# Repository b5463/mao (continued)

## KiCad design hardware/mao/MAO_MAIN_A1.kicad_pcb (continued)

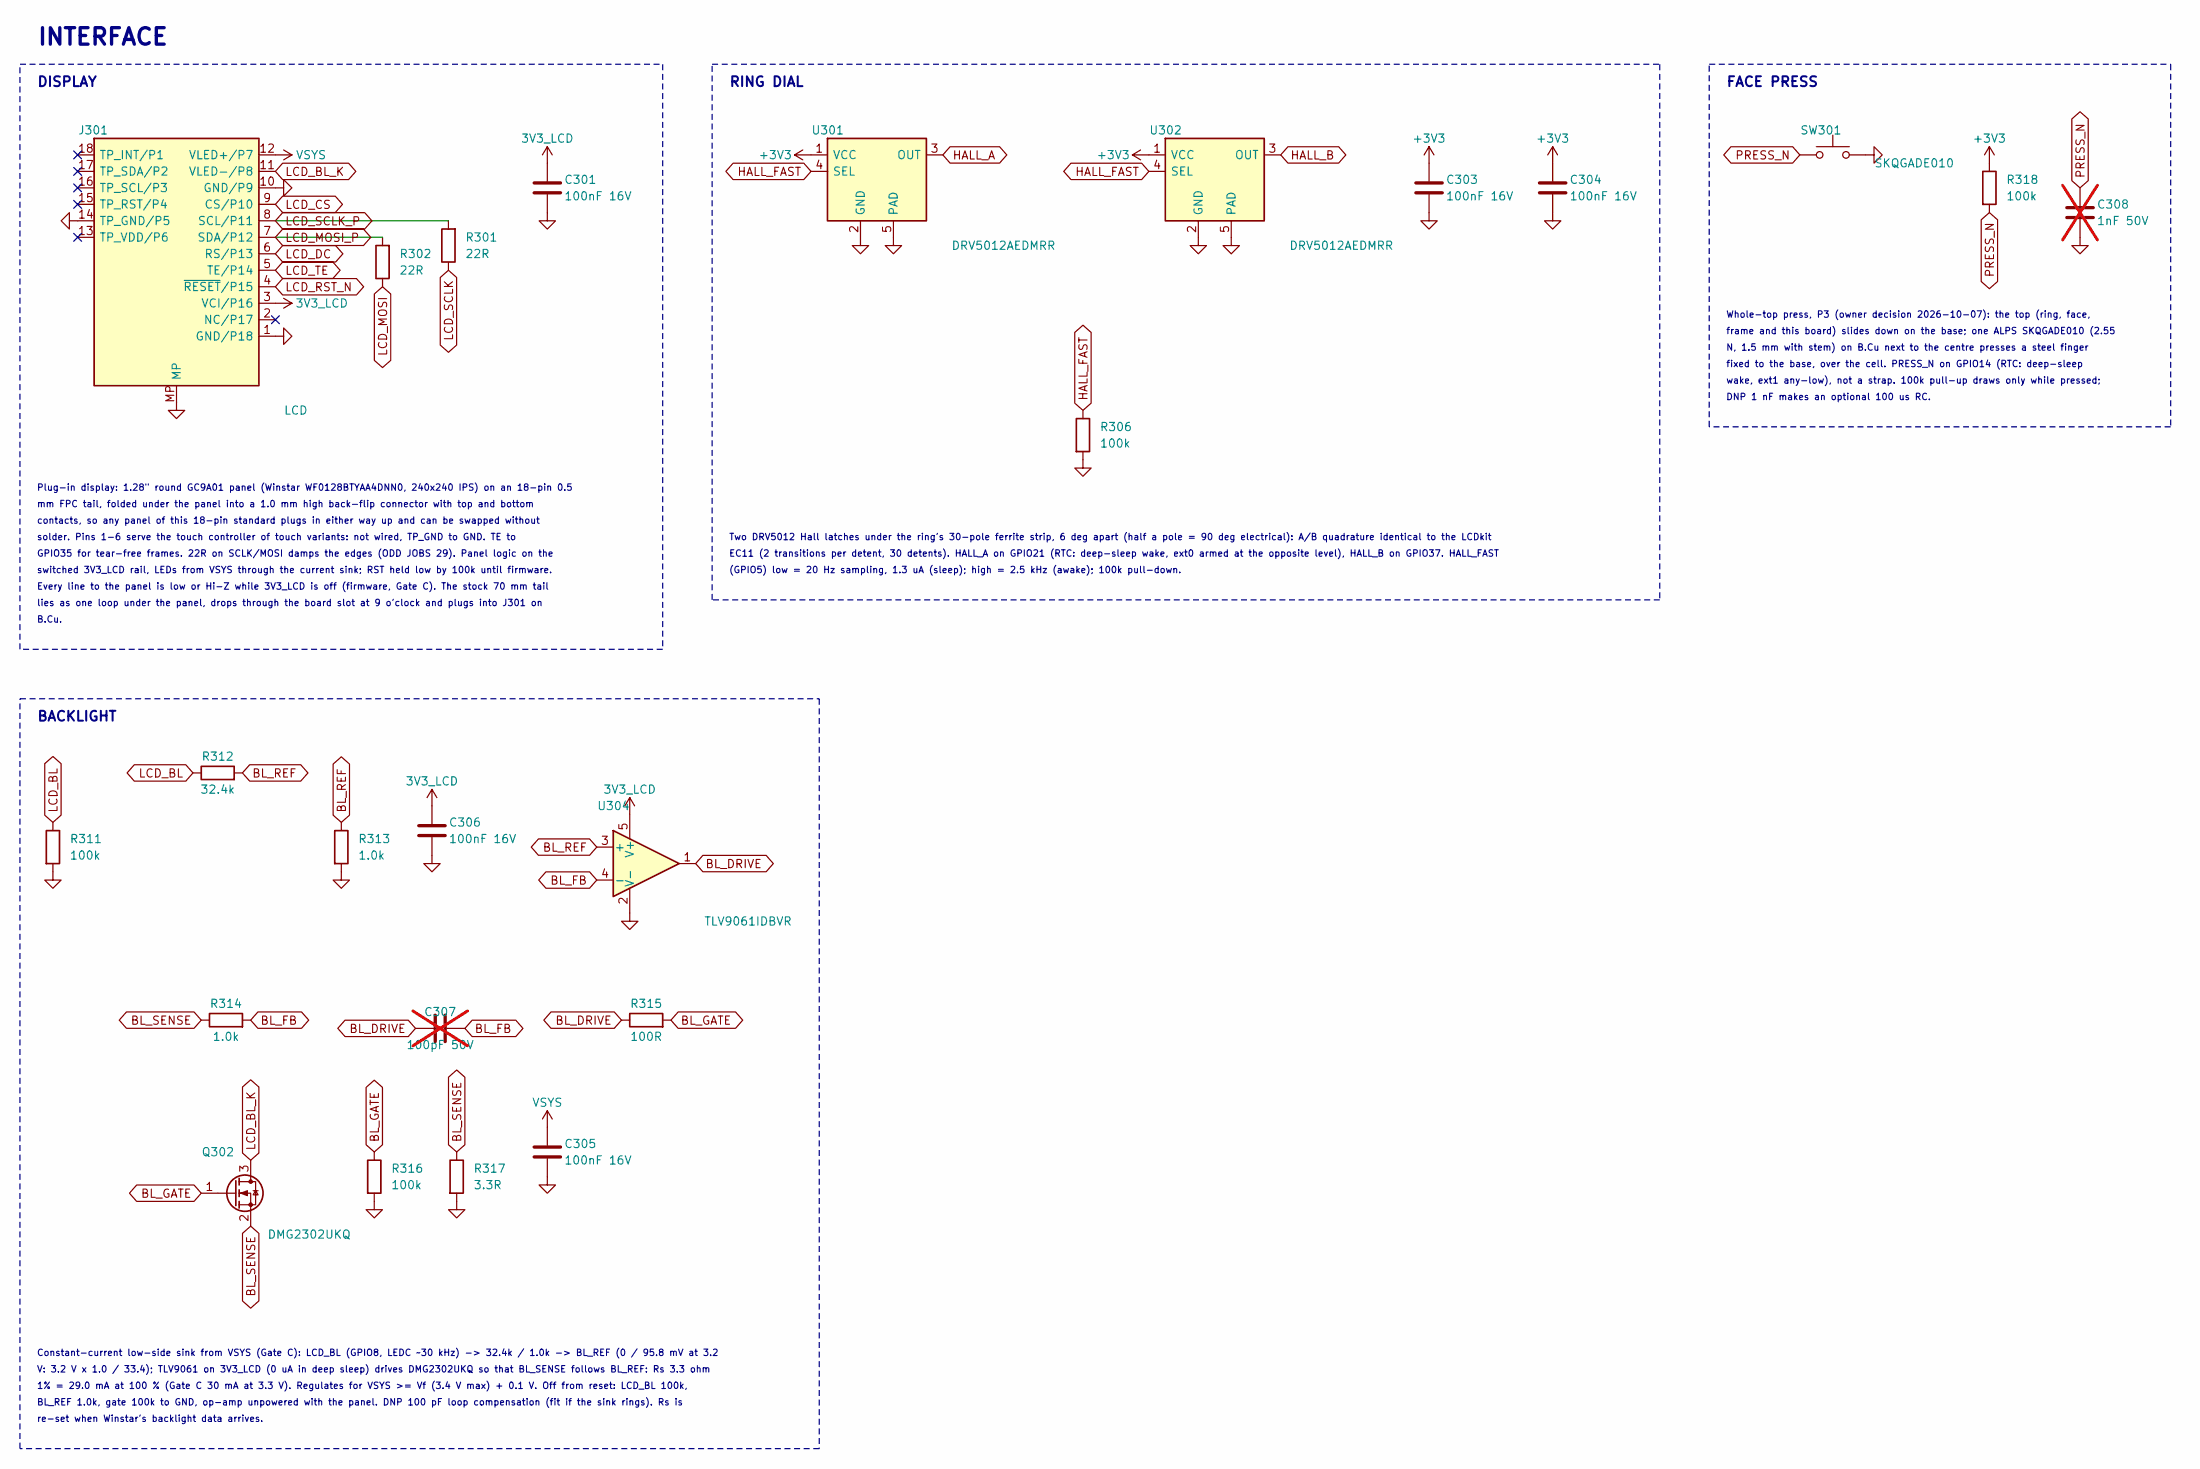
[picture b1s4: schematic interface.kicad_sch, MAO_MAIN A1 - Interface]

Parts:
C301, C303, C304, C305, C306: 100nF 16V; C_0402_1005Metric; MPN CL05B104KO5NNNC; LCSC C1525
C307: 100pF 50V; C_0402_1005Metric; MPN CL05C101JB5NNNC; LCSC C26409; not fitted
C308: 1nF 50V; C_0402_1005Metric; MPN CL05B102KB5NNNC; LCSC C14442; not fitted
J301: LCD; HDGC_0.5K-HX-18PWB_1x18-1MP_P0.5mm_Horizontal; MPN 0.5K-HX-18PWB; LCSC C2919497
Q302: DMG2302UKQ; SOT-23; MPN DMG2302UKQ-7; LCSC C5224573
R301, R302: 22R; R_0402_1005Metric; MPN 0402WGF220JTCE; LCSC C25092
R306, R311, R316, R318: 100k; R_0402_1005Metric; MPN 0402WGF1003TCE; LCSC C25741
R312: 32.4k; R_0402_1005Metric; MPN 0402WGF3242TCE; LCSC C26974
R313, R314: 1.0k; R_0402_1005Metric; MPN 0402WGF1001TCE; LCSC C11702
R315: 100R; R_0402_1005Metric; MPN 0402WGF1000TCE; LCSC C25076
R317: 3.3R; R_0603_1608Metric; MPN 0603WAF330KT5E; LCSC C22979
SW301: SKQGADE010; SW_SPST_SKQG_WithStem; MPN SKQGADE010; LCSC C116647
U301, U302: DRV5012AEDMRR; Texas_X2SON-4-1EP_1.1x1.4mm_P0.5mm_EP0.8x0.6mm; MPN DRV5012AEDMRR; LCSC C2655038
U304: TLV9061IDBVR; SOT-23-5; MPN TLV9061IDBVR; LCSC C398358

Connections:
3V3_LCD: C301.1, C306.1, J301.3 (VCI/P16), U304.5 (V+); also elsewhere on the board
+3V3: C303.1, C304.1, R318.1, U301.1 (VCC), U302.1 (VCC); also elsewhere on the board
BL_DRIVE: C307.1, R315.1, U304.1
BL_FB: C307.2, R314.2, U304.4 (-)
BL_GATE: Q302.1 (G), R315.2, R316.1
BL_REF: R312.2, R313.1, U304.3 (+)
BL_SENSE: Q302.2 (S), R314.1, R317.1
GND: C301.2, C303.2, C304.2, C305.2, C306.2, C308.2, J301.1 (GND/P18), J301.10 (GND/P9), J301.14 (TP_GND/P5), J301.MP, R306.2, R311.2, R313.2, R316.2, R317.2, SW301.2, U301.2 (GND), U301.5 (PAD), U302.2 (GND), U302.5 (PAD), U304.2 (V-); also elsewhere on the board
HALL_A: U301.3 (OUT); also elsewhere on the board
HALL_B: U302.3 (OUT); also elsewhere on the board
HALL_FAST: R306.1, U301.4 (SEL), U302.4 (SEL); also elsewhere on the board
LCD_BL: R311.1, R312.1; also elsewhere on the board
LCD_BL_K: J301.11 (VLED-/P8), Q302.3 (D)
LCD_CS: J301.9 (CS/P10); also elsewhere on the board
LCD_DC: J301.6 (RS/P13); also elsewhere on the board
LCD_MOSI: R302.1; also elsewhere on the board
LCD_MOSI_P: J301.7 (SDA/P12), R302.2
LCD_RST_N: J301.4 (~RESET/P15); also elsewhere on the board
LCD_SCLK: R301.1; also elsewhere on the board
LCD_SCLK_P: J301.8 (SCL/P11), R301.2
LCD_TE: J301.5 (TE/P14); also elsewhere on the board
PRESS_N: C308.1, R318.2, SW301.1; also elsewhere on the board
VSYS: C305.1, J301.12 (VLED+/P7); also elsewhere on the board

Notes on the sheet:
INTERFACE
DISPLAY
Plug-in display: 1.28" round GC9A01 panel (Winstar WF0128BTYAA4DNN0, 240x240 IPS) on an 18-pin 0.5
mm FPC tail, folded under the panel into a 1.0 mm high back-flip connector with top and bottom
contacts, so any panel of this 18-pin standard plugs in either way up and can be swapped without
solder. Pins 1-6 serve the touch controller of touch variants: not wired, TP_GND to GND. TE to
GPIO35 for tear-free frames. 22R on SCLK/MOSI damps the edges (ODD JOBS 29). Panel logic on the
switched 3V3_LCD rail, LEDs from VSYS through the current sink; RST held low by 100k until firmware.
Every line to the panel is low or Hi-Z while 3V3_LCD is off (firmware, Gate C). The stock 70 mm tail
lies as one loop under the panel, drops through the board slot at 9 o'clock and plugs into J301 on
B.Cu.
RING DIAL
Two DRV5012 Hall latches under the ring's 30-pole ferrite strip, 6 deg apart (half a pole = 90 deg electrical): A/B quadrature identical to the LCDkit
EC11 (2 transitions per detent, 30 detents). HALL_A on GPIO21 (RTC: deep-sleep wake, ext0 armed at the opposite level), HALL_B on GPIO37. HALL_FAST
(GPIO5) low = 20 Hz sampling, 1.3 uA (sleep); high = 2.5 kHz (awake); 100k pull-down.
FACE PRESS
Whole-top press, P3 (owner decision 2026-10-07): the top (ring, face,
frame and this board) slides down on the base; one ALPS SKQGADE010 (2.55
N, 1.5 mm with stem) on B.Cu next to the centre presses a steel finger
fixed to the base, over the cell. PRESS_N on GPIO14 (RTC: deep-sleep
wake, ext1 any-low), not a strap. 100k pull-up draws only while pressed;
DNP 1 nF makes an optional 100 us RC.
BACKLIGHT
Constant-current low-side sink from VSYS (Gate C): LCD_BL (GPIO8, LEDC ~30 kHz) -> 32.4k / 1.0k -> BL_REF (0 / 95.8 mV at 3.2
V: 3.2 V x 1.0 / 33.4); TLV9061 on 3V3_LCD (0 uA in deep sleep) drives DMG2302UKQ so that BL_SENSE follows BL_REF: Rs 3.3 ohm
1% = 29.0 mA at 100 % (Gate C 30 mA at 3.3 V). Regulates for VSYS >= Vf (3.4 V max) + 0.1 V. Off from reset: LCD_BL 100k,
BL_REF 1.0k, gate 100k to GND, op-amp unpowered with the panel. DNP 100 pF loop compensation (fit if the sink rings). Rs is
re-set when Winstar's backlight data arrives.

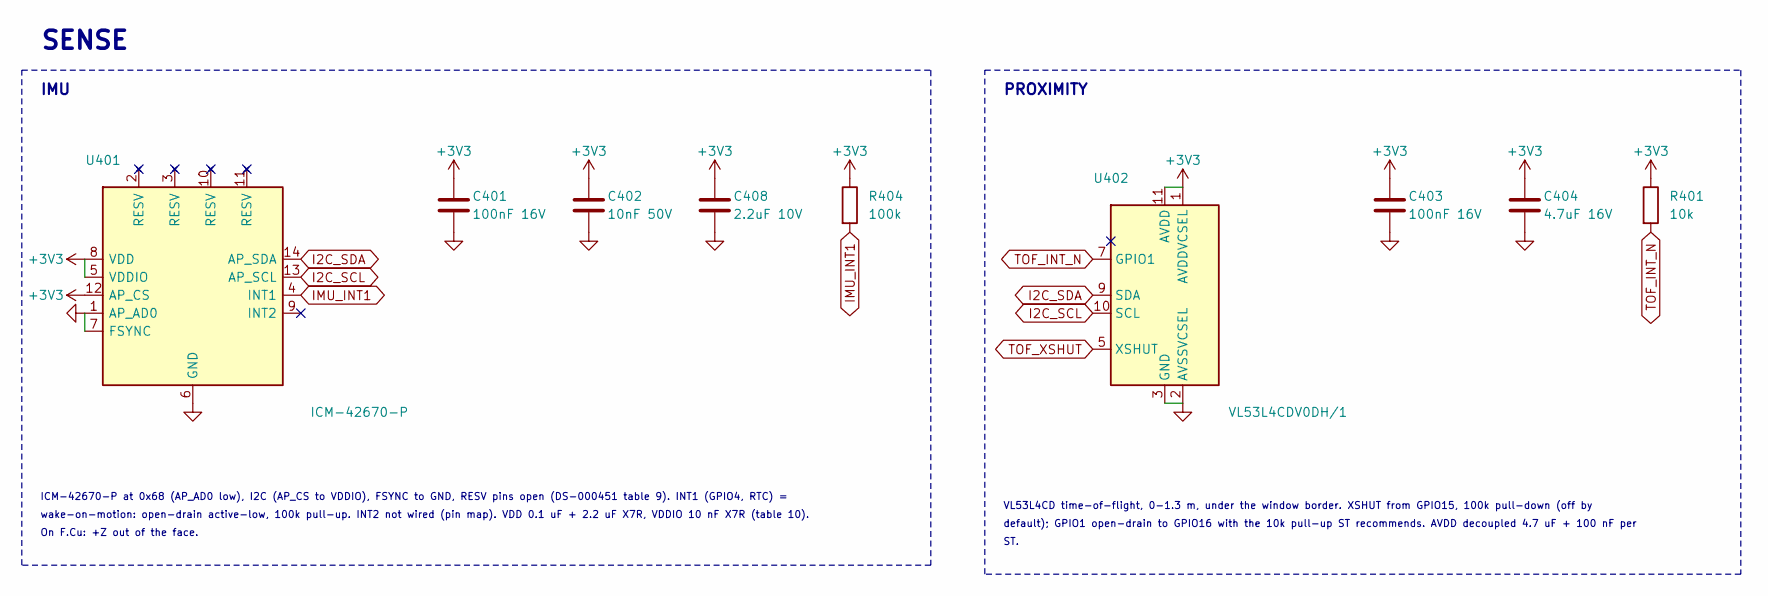
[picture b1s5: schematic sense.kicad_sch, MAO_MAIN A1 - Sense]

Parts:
C401, C403: 100nF 16V; C_0402_1005Metric; MPN CL05B104KO5NNNC; LCSC C1525
C402: 10nF 50V; C_0402_1005Metric; MPN CL05B103KB5NNNC; LCSC C15195
C404: 4.7uF 16V; C_0603_1608Metric; MPN CL10A475KO8NNNC; LCSC C19666
C408: 2.2uF 10V; C_0603_1608Metric; MPN CL10B225KP8NNNC; LCSC C100082
R401: 10k; R_0402_1005Metric; MPN 0402WGF1002TCE; LCSC C25744
R404: 100k; R_0402_1005Metric; MPN 0402WGF1003TCE; LCSC C25741
U401: ICM-42670-P; LGA-14_3x2.5mm_P0.5mm_LayoutBorder3x4y; MPN ICM-42670-P; LCSC C3288646
U402: VL53L4CDV0DH/1; ST_VL53L0X; MPN VL53L4CDV0DH/1; LCSC C3178291

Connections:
+3V3: C401.1, C402.1, C403.1, C404.1, C408.1, R401.1, R404.1, U401.5 (VDDIO), U401.8 (VDD), U401.12 (AP_CS), U402.1 (AVDDVCSEL), U402.11 (AVDD); also elsewhere on the board
GND: C401.2, C402.2, C403.2, C404.2, C408.2, U401.1 (AP_AD0), U401.6 (GND), U401.7 (FSYNC), U402.2 (AVSSVCSEL), U402.3 (GND), U402.4 (GND), U402.6 (GND), U402.12 (GND); also elsewhere on the board
I2C_SCL: U401.13 (AP_SCL), U402.10 (SCL); also elsewhere on the board
I2C_SDA: U401.14 (AP_SDA), U402.9 (SDA); also elsewhere on the board
IMU_INT1: R404.2, U401.4 (INT1); also elsewhere on the board
TOF_INT_N: R401.2, U402.7 (GPIO1); also elsewhere on the board
TOF_XSHUT: U402.5 (XSHUT); also elsewhere on the board

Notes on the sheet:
SENSE
IMU
ICM-42670-P at 0x68 (AP_AD0 low), I2C (AP_CS to VDDIO), FSYNC to GND, RESV pins open (DS-000451 table 9). INT1 (GPIO4, RTC) =
wake-on-motion: open-drain active-low, 100k pull-up. INT2 not wired (pin map). VDD 0.1 uF + 2.2 uF X7R, VDDIO 10 nF X7R (table 10).
On F.Cu: +Z out of the face.
PROXIMITY
VL53L4CD time-of-flight, 0-1.3 m, under the window border. XSHUT from GPIO15, 100k pull-down (off by
default); GPIO1 open-drain to GPIO16 with the 10k pull-up ST recommends. AVDD decoupled 4.7 uF + 100 nF per
ST.

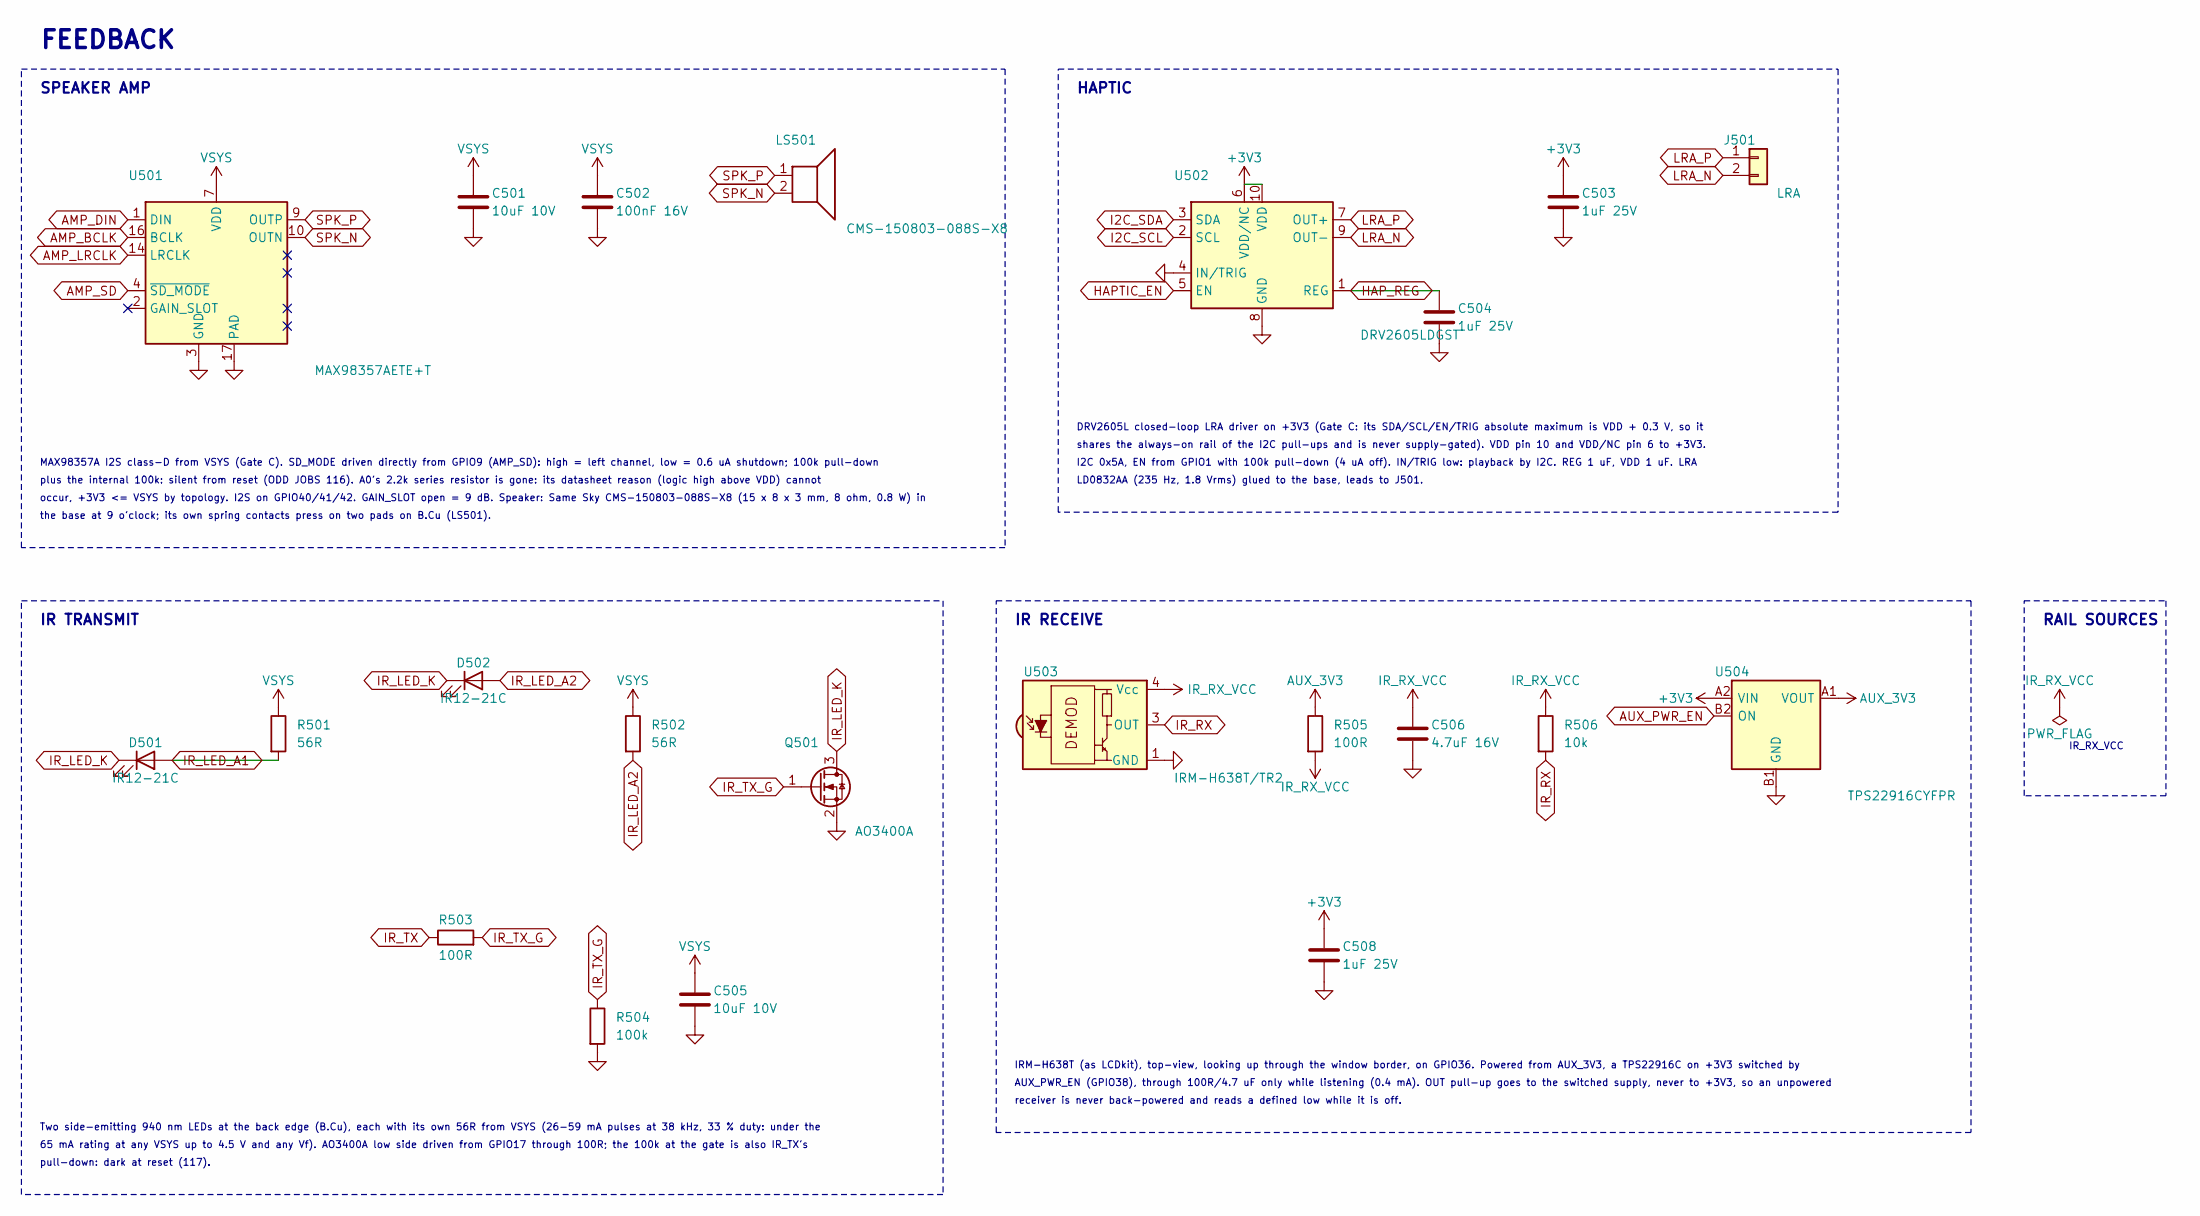
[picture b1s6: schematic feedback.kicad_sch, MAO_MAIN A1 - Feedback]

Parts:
C501, C505: 10uF 10V; C_0603_1608Metric; MPN CL10A106KP8NNNC; LCSC C19702
C502: 100nF 16V; C_0402_1005Metric; MPN CL05B104KO5NNNC; LCSC C1525
C503, C504, C508: 1uF 25V; C_0402_1005Metric; MPN CL05A105KA5NQNC; LCSC C52923
C506: 4.7uF 16V; C_0603_1608Metric; MPN CL10A475KO8NNNC; LCSC C19666
D501, D502: IR12-21C; Everlight_IR12-21C_RightAngle_3x1mm; MPN IR12-21C/TR8; LCSC C53672
J501: LRA; WirePads_1x02_P2.5mm_1.0x1.8mm; MPN PCB feature: LD0832AA-0099F leads
LS501: CMS-150803-088S-X8; SameSky_CMS-150803_SpringPads; MPN CMS-150803-088S-X8
Q501: AO3400A; SOT-23; MPN AO3400A; LCSC C20917
R501, R502: 56R; R_0603_1608Metric; MPN 0603WAF560JT5E; LCSC C25196
R503, R505: 100R; R_0402_1005Metric; MPN 0402WGF1000TCE; LCSC C25076
R504: 100k; R_0402_1005Metric; MPN 0402WGF1003TCE; LCSC C25741
R506: 10k; R_0402_1005Metric; MPN 0402WGF1002TCE; LCSC C25744
U501: MAX98357AETE+T; TQFN-16-1EP_3x3mm_P0.5mm_EP1.23x1.23mm_ThermalVias; MPN MAX98357AETE+T; LCSC C910544
U502: DRV2605LDGST; MSOP-10_3x3mm_P0.5mm; MPN DRV2605LDGST; LCSC C425927
U503: IRM-H638T/TR2; Everlight_IRM-H6xxT; MPN IRM-H638T/TR2; LCSC C91447
U504: TPS22916CYFPR; Texas_PicoStar_BGA-4_0.758x0.758mm_Layout2x2_P0.4mm; MPN TPS22916CYFPR; LCSC C2680319

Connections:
+3V3: C503.1, C508.1, U502.6 (VDD/NC), U502.10 (VDD), U504.A2 (VIN); also elsewhere on the board
AMP_BCLK: U501.16 (BCLK); also elsewhere on the board
AMP_DIN: U501.1 (DIN); also elsewhere on the board
AMP_LRCLK: U501.14 (LRCLK); also elsewhere on the board
AMP_SD: U501.4 (~SD_MODE); also elsewhere on the board
AUX_3V3: R505.1, U504.A1 (VOUT)
AUX_PWR_EN: U504.B2 (ON); also elsewhere on the board
GND: C501.2, C502.2, C503.2, C504.2, C505.2, C506.2, C508.2, Q501.2 (S), R504.2, U501.3 (GND), U501.11 (GND), U501.15 (GND), U501.17 (PAD), U502.4 (IN/TRIG), U502.8 (GND), U503.1 (GND), U503.2 (GND), U504.B1 (GND); also elsewhere on the board
HAPTIC_EN: U502.5 (EN); also elsewhere on the board
HAP_REG: C504.1, U502.1 (REG)
I2C_SCL: U502.2 (SCL); also elsewhere on the board
I2C_SDA: U502.3 (SDA); also elsewhere on the board
IR_LED_A1: D501.2 (A), R501.2
IR_LED_A2: D502.2 (A), R502.2
IR_LED_K: D501.1 (K), D502.1 (K), Q501.3 (D)
IR_RX: R506.2, U503.3 (OUT); also elsewhere on the board
IR_RX_VCC: C506.1, R505.2, R506.1, U503.4 (Vcc); also elsewhere on the board
IR_TX: R503.1; also elsewhere on the board
IR_TX_G: Q501.1 (G), R503.2, R504.1
LRA_N: J501.2, U502.9 (OUT-)
LRA_P: J501.1, U502.7 (OUT+)
SPK_N: LS501.2, U501.10 (OUTN)
SPK_P: LS501.1, U501.9 (OUTP)
VSYS: C501.1, C502.1, C505.1, R501.1, R502.1, U501.7 (VDD), U501.8 (VDD); also elsewhere on the board

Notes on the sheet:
FEEDBACK
SPEAKER AMP
MAX98357A I2S class-D from VSYS (Gate C). SD_MODE driven directly from GPIO9 (AMP_SD): high = left channel, low = 0.6 uA shutdown; 100k pull-down
plus the internal 100k: silent from reset (ODD JOBS 116). A0's 2.2k series resistor is gone: its datasheet reason (logic high above VDD) cannot
occur, +3V3 <= VSYS by topology. I2S on GPIO40/41/42. GAIN_SLOT open = 9 dB. Speaker: Same Sky CMS-150803-088S-X8 (15 x 8 x 3 mm, 8 ohm, 0.8 W) in
the base at 9 o'clock; its own spring contacts press on two pads on B.Cu (LS501).
HAPTIC
DRV2605L closed-loop LRA driver on +3V3 (Gate C: its SDA/SCL/EN/TRIG absolute maximum is VDD + 0.3 V, so it
shares the always-on rail of the I2C pull-ups and is never supply-gated). VDD pin 10 and VDD/NC pin 6 to +3V3.
I2C 0x5A, EN from GPIO1 with 100k pull-down (4 uA off). IN/TRIG low: playback by I2C. REG 1 uF, VDD 1 uF. LRA
LD0832AA (235 Hz, 1.8 Vrms) glued to the base, leads to J501.
IR TRANSMIT
Two side-emitting 940 nm LEDs at the back edge (B.Cu), each with its own 56R from VSYS (26-59 mA pulses at 38 kHz, 33 % duty: under the
65 mA rating at any VSYS up to 4.5 V and any Vf). AO3400A low side driven from GPIO17 through 100R; the 100k at the gate is also IR_TX's
pull-down: dark at reset (117).
IR RECEIVE
IRM-H638T (as LCDkit), top-view, looking up through the window border, on GPIO36. Powered from AUX_3V3, a TPS22916C on +3V3 switched by
AUX_PWR_EN (GPIO38), through 100R/4.7 uF only while listening (0.4 mA). OUT pull-up goes to the switched supply, never to +3V3, so an unpowered
receiver is never back-powered and reads a defined low while it is off.
RAIL SOURCES
IR_RX_VCC

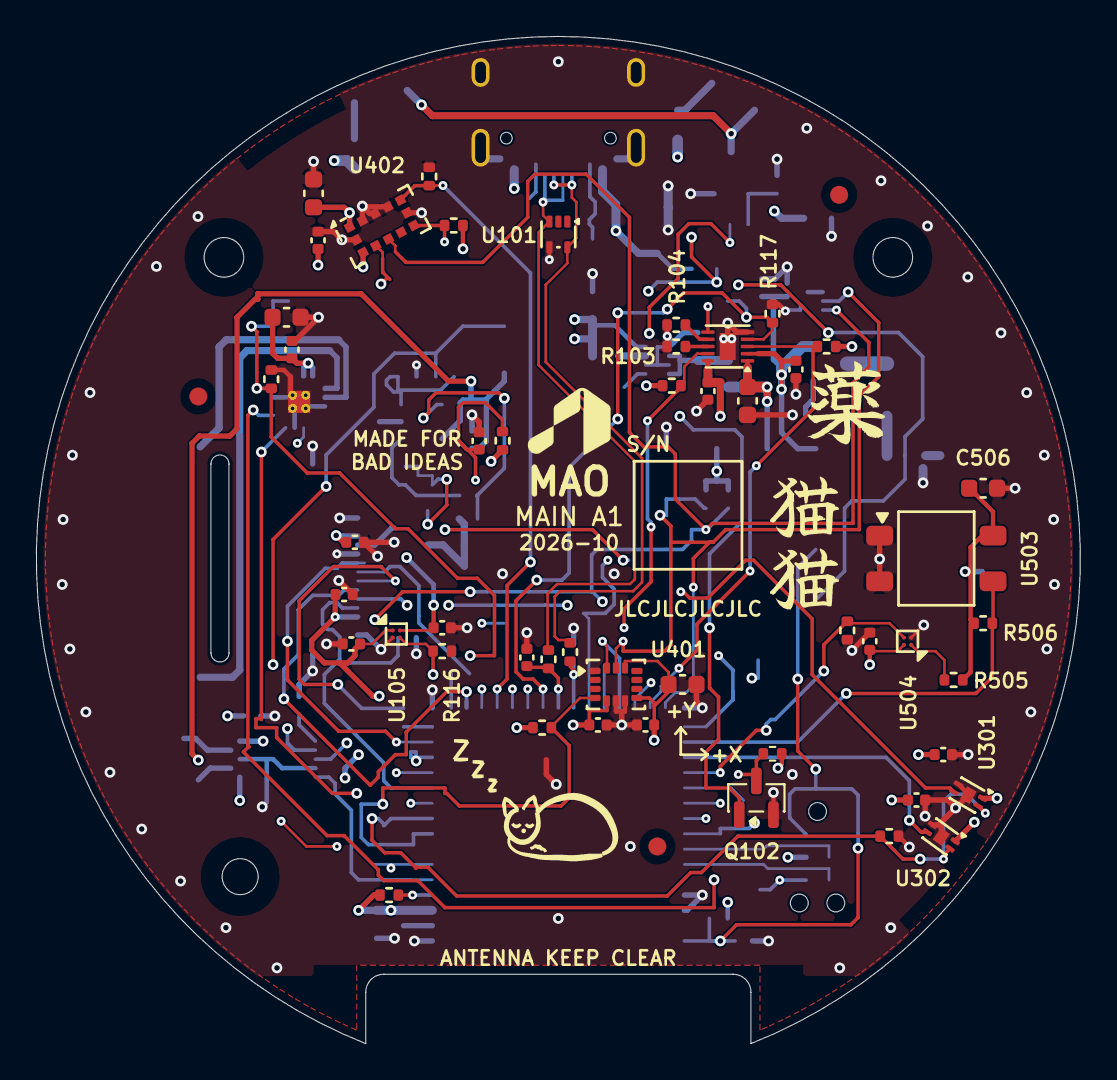
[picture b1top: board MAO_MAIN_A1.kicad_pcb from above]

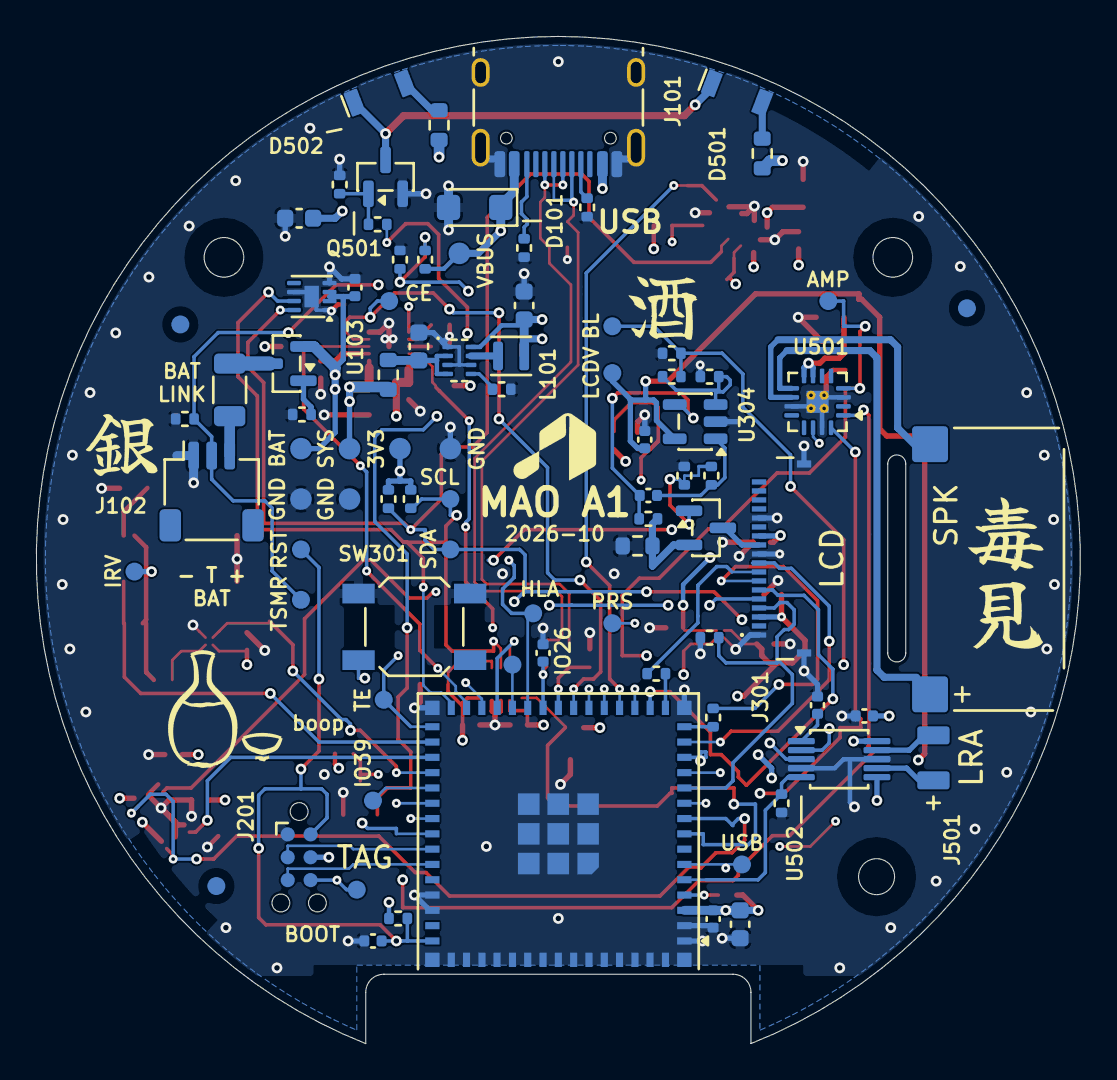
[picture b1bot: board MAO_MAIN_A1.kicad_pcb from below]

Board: 4 copper layers, 58.0 x 56.0 mm, 140 parts (85 on the bottom side), 76 nets.

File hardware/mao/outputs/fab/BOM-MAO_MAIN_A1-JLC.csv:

Comment,Designator,Footprint,LCSC Part #,Manufacturer Part,Manufacturer,Quantity,JLC Part Type,JLC Stock 2026-10-06,Sourcing Note
2.2uF 25V,"C101,C103",C_0402_1005Metric,C307418,CL05A225KA5NUNC,Samsung,2,Extended,897637,no Basic/Preferred 2.2u 25 V 0402 in the JLC library (review 2026-10-06)
10uF 25V,C102,C_0603_1608Metric,C96446,CL10A106MA8NRNC,Samsung,1,Basic,3300000,
100nF 16V,"C104,C202,C301,C303,C304,C305,C306,C401,C403,C502",C_0402_1005Metric,C1525,CL05B104KO5NNNC,Samsung,10,Basic,22000000,LCSC shop stock 0 on 2026-10-06; JLC assembly stock fine
4.7uF 16V,"C105,C404,C506",C_0603_1608Metric,C19666,CL10A475KO8NNNC,Samsung,3,Basic,2500000,
10uF 10V,"C106,C501,C505",C_0603_1608Metric,C19702,CL10A106KP8NNNC,Samsung,3,Basic,10300000,
1uF 25V,"C109,C110,C203,C503,C504,C508",C_0402_1005Metric,C52923,CL05A105KA5NQNC,Samsung,6,Basic,8300000,
22uF 6.3V,C201,C_0603_1608Metric,C59461,CL10A226MQ8NRNC,Samsung,1,Basic,8000000,
10nF 50V,C402,C_0402_1005Metric,C15195,CL05B103KB5NNNC,Samsung,1,Basic,3900000,
2.2uF 10V,C408,C_0603_1608Metric,C100082,CL10B225KP8NNNC,Samsung,1,Extended,354360,no Basic 2.2u X7R 0603 (Basic C23630 is X5R)
SMF15A,D101,D_SMF,C123802,SMF15A,MDD,1,Extended,61610,
IR12-21C,"D501,D502",Everlight_IR12-21C_RightAngle_3x1mm,C53672,IR12-21C/TR8,Everlight,2,Extended,12341,
USB-C,J101,USB_C_Receptacle_HRO_TYPE-C-31-M-12,C165948,TYPE-C-31-M-12,Korean Hroparts,1,Extended,420357,
BAT,J102,JST_SH_SM03B-SRSS-TB_1x03-1MP_P1.00mm_Horizontal,C7430445,ZX-SH1.0-3PWT (JST SM03B-SRSS-TB compatible),Megastar,1,Extended,90750,JST SH-compatible 3-pin (battery)
LCD,J301,HDGC_0.5K-HX-18PWB_1x18-1MP_P0.5mm_Horizontal,C2919497,0.5K-HX-18PWB,HDGC,1,Extended,16270,listed as HDGC 0.5K-HX-18PWB (same part)
2.2uH,L101,L_Murata_DFE201610P,C337893,DFE201612E-2R2M=P2,Murata,1,Extended,33137,
AO3401A,Q101,SOT-23,C15127,AO3401A,AOS,1,Basic,814915,
2N7002,Q102,SOT-23,C8545,2N7002,CJ,1,Basic,1576966,
DMG2302UKQ,Q302,SOT-23,C5224573,DMG2302UKQ-7,Diodes,1,Extended,990,"DMG2302UKQ-7: the automotive-qualified DMG2302UK-7 (C460977, 124 left), same SOT-23 pinout"
AO3400A,Q501,SOT-23,C20917,AO3400A,AOS,1,Basic,953963,
5.1k,"R101,R102",R_0402_1005Metric,C25905,0402WGF5101TCE,UNI-ROYAL,2,Basic,5900000,
1.43k,R103,R_0402_1005Metric,C163483,RC0402FR-071K43L,YAGEO,1,Extended,9576,no Basic 1.43k 0402
18k,R104,R_0402_1005Metric,C25762,0402WGF1802TCE,UNI-ROYAL,1,Preferred Extended,468801,no Basic 18k 0402
0R,R108,R_1206_3216Metric,C17888,1206W4F0000T5E,UNI-ROYAL,1,Basic,2600000,
10k,"R109,R118,R119,R201,R202,R401,R506",R_0402_1005Metric,C25744,0402WGF1002TCE,UNI-ROYAL,7,Basic,21500000,
102k,R111,R_0402_1005Metric,C2933066,FRC0402F1023TS,FOJAN,1,Extended,177764,no Basic 102k 0402
100k,"R116,R117,R120,R123,R207,R208,R209,R210,R211,R306,R311,R316,R318,R404,R504",R_0402_1005Metric,C25741,0402WGF1003TCE,UNI-ROYAL,15,Basic,8200000,
150k,R121,R_0402_1005Metric,C25755,0402WGF1503TCE,UNI-ROYAL,1,Preferred Extended,270669,no Basic 150k 0402
0R,R122,R_0603_1608Metric,C21189,0603WAF0000T5E,UNI-ROYAL,1,Basic,23600000,
4.7k,"R213,R214",R_0402_1005Metric,C25900,0402WGF4701TCE,UNI-ROYAL,2,Basic,15400000,
22R,"R215,R216,R301,R302",R_0402_1005Metric,C25092,0402WGF220JTCE,UNI-ROYAL,4,Basic,4600000,
32.4k,R312,R_0402_1005Metric,C26974,0402WGF3242TCE,UNI-ROYAL,1,Extended,37795,no Basic 32.4k 0402
1.0k,"R313,R314",R_0402_1005Metric,C11702,0402WGF1001TCE,UNI-ROYAL,2,Basic,7000000,LCSC shop stock 0 on 2026-10-06; JLC assembly stock fine
100R,"R315,R503,R505",R_0402_1005Metric,C25076,0402WGF1000TCE,UNI-ROYAL,3,Basic,4000000,LCSC shop stock 0 on 2026-10-06; JLC assembly stock fine
3.3R,R317,R_0603_1608Metric,C22979,0603WAF330KT5E,UNI-ROYAL,1,Extended,280671,no Basic 3.3R 0603
56R,"R501,R502",R_0603_1608Metric,C25196,0603WAF560JT5E,UNI-ROYAL,2,Preferred Extended,1070000,no Basic 56R 0603
SKQGADE010,SW301,SW_SPST_SKQG_WithStem,C116647,SKQGADE010,ALPS,1,Extended,49220,"whole-top press, 1 per board (owner decision 2026-10-07); LCSC stock 2026-10-07, JLC library type to confirm at order"
TPD2E2U06,U101,SOT-553,C1972959,TPD2E2U06DRLR,TI,1,Extended,7569,
BQ25185DLHR,U102,Texas_DLH0010A_WSON-10-1EP_2.2x2mm_P0.4mm_EP0.9x1.5mm,C19725033,BQ25185DLHR,TI,1,Extended,3623,
MAX17048G+T10,U103,TDFN-8-1EP_2x2mm_P0.5mm_EP0.8x1.2mm,C2682616,MAX17048G+T10,Analog Devices,1,Extended,25799,
TPS62840DLCR,U104,TI_DLC0008B_VSON-HR-8_1.5x2mm_P0.5mm,C2071859,TPS62840DLCR,TI,1,Extended,3882,
TPS22916CYFPR,"U105,U504",Texas_PicoStar_BGA-4_0.758x0.758mm_Layout2x2_P0.4mm,C2680319,TPS22916CYFPR,TI,2,Extended,77,"LOW STOCK (2 per board, enough for the 5-unit build); 0.4 mm WCSP: order JLC Standard PCBA. Fallback TPS22916BYFPR C2150095 (21,486): fast rise, check the 3V3_LCD / AUX_3V3 inrush"
ESP32-S3-MINI-1-N8,U201,ESP32-S2-MINI-1,C2913206,ESP32-S3-MINI-1-N8,Espressif,1,Extended,6018,
DRV5012AEDMRR,"U301,U302",Texas_X2SON-4-1EP_1.1x1.4mm_P0.5mm_EP0.8x0.6mm,C2655038,DRV5012AEDMRR,TI,2,Extended,5226,
TLV9061IDBVR,U304,SOT-23-5,C398358,TLV9061IDBVR,TI,1,Extended,289451,
ICM-42670-P,U401,LGA-14_3x2.5mm_P0.5mm_LayoutBorder3x4y,C3288646,ICM-42670-P,TDK InvenSense,1,Extended,6692,
VL53L4CDV0DH/1,U402,ST_VL53L0X,C3178291,VL53L4CDV0DH/1,ST,1,Extended,11527,
MAX98357AETE+T,U501,TQFN-16-1EP_3x3mm_P0.5mm_EP1.23x1.23mm_ThermalVias,C910544,MAX98357AETE+T,Analog Devices,1,Extended,25277,
DRV2605LDGST,U502,MSOP-10_3x3mm_P0.5mm,C425927,DRV2605LDGST,TI,1,Extended,858,DRV2605LDGST: the DGSR part on a 250-piece reel (review 2026-10-06)
IRM-H638T/TR2,U503,Everlight_IRM-H6xxT,C91447,IRM-H638T/TR2,Everlight,1,Extended,177048,
